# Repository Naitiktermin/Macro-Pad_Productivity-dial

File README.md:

# Macro-Pad_Productivity-dial
Schematics and code for a macro pad with a productivity dial.

Macro-Pad Top-
  Top View:

  Bottom View:

Macro-Pad Base-
    Top View:

  Bottom View:

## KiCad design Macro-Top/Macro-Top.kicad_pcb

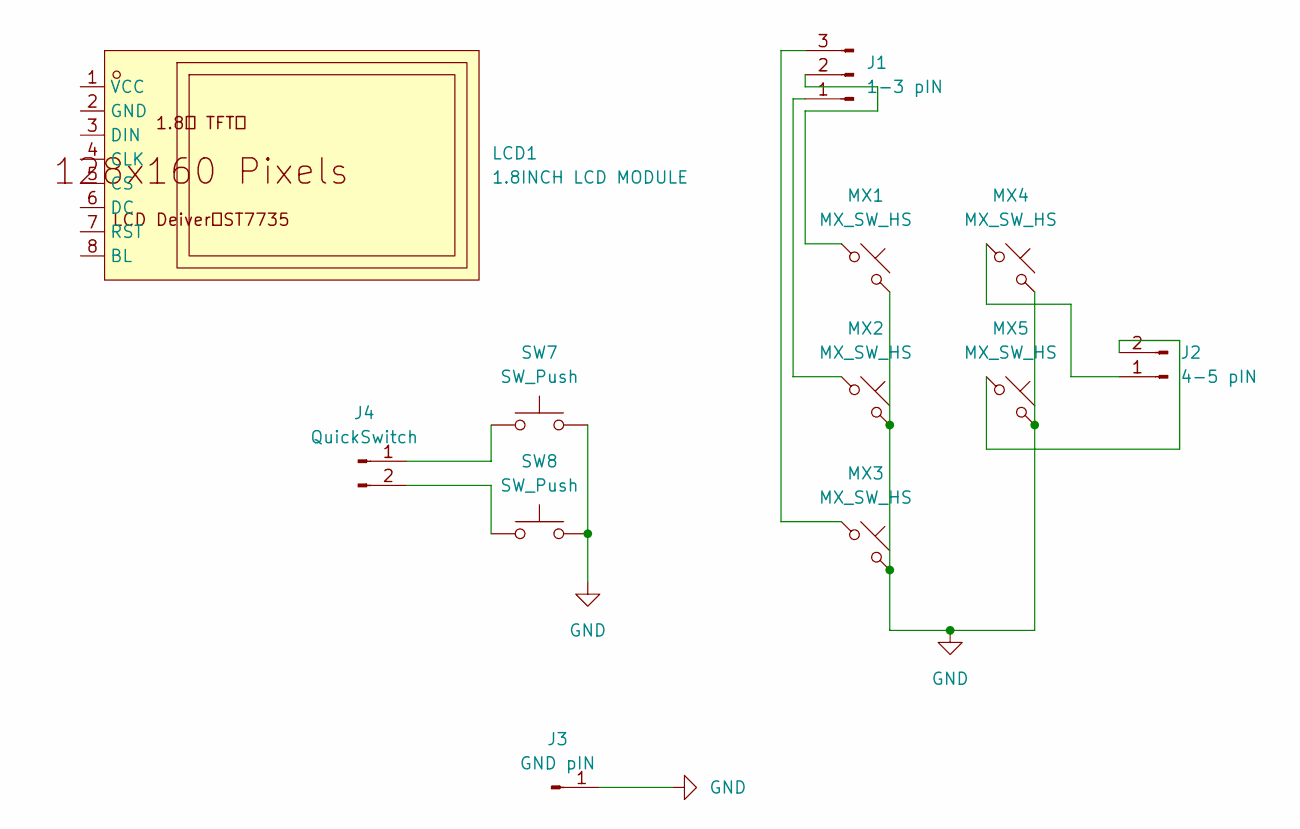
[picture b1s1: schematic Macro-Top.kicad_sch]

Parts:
J1: 1-3 pIN; PinHeader_1x03_P2.54mm_Vertical
J2: 4-5 pIN; PinHeader_1x02_P2.54mm_Vertical
J3: GND pIN; PinHeader_1x01_P2.54mm_Vertical
J4: QuickSwitch; PinHeader_1x02_P2.54mm_Horizontal
LCD1: 1.8INCH LCD MODULE; LCD-TH_L56.5-W34.0_1-8INCH-LCD-MODULE; MPN 1.8inch LCD Module; LCSC Part C359940
MX1, MX2, MX3, MX4, MX5: MX_SW_HS; SW_MX_HS_CPG151101S11_1u
SW7, SW8: SW_Push; SW_PUSH_6mm

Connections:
GND: J3.1 (Pin_1_1), MX1.2, MX2.2, MX3.2, MX4.2, MX5.2, SW7.2, SW8.2
unnamed: J1.1, MX2.1
unnamed: J1.2, MX1.1
unnamed: J1.3, MX3.1
unnamed: J2.1, MX4.1
unnamed: J2.2, MX5.1
unnamed: J4.1, SW7.1
unnamed: J4.2, SW8.1

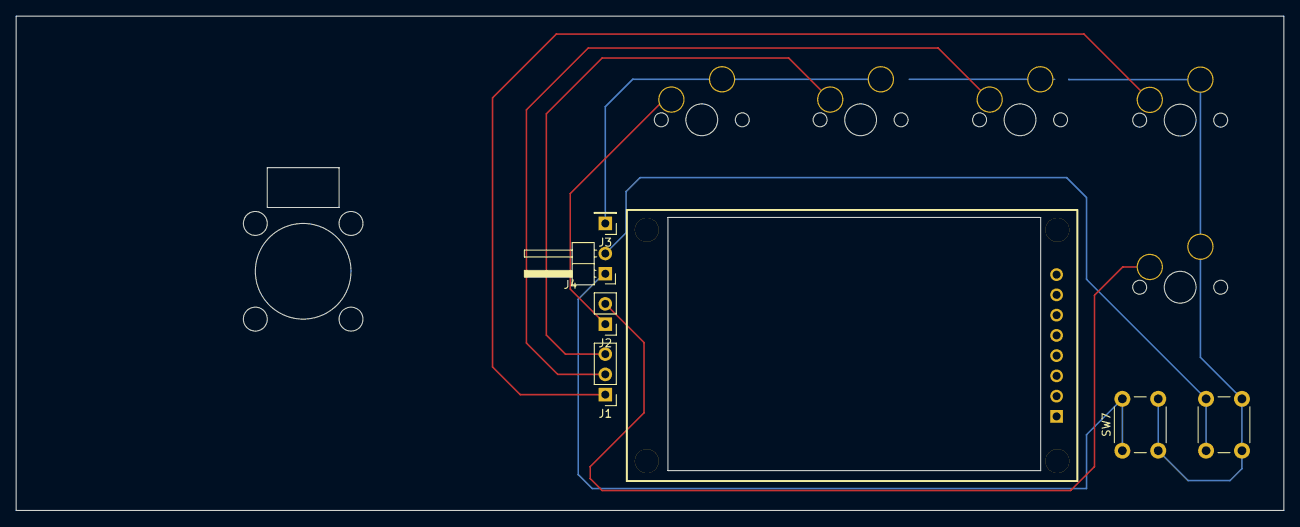
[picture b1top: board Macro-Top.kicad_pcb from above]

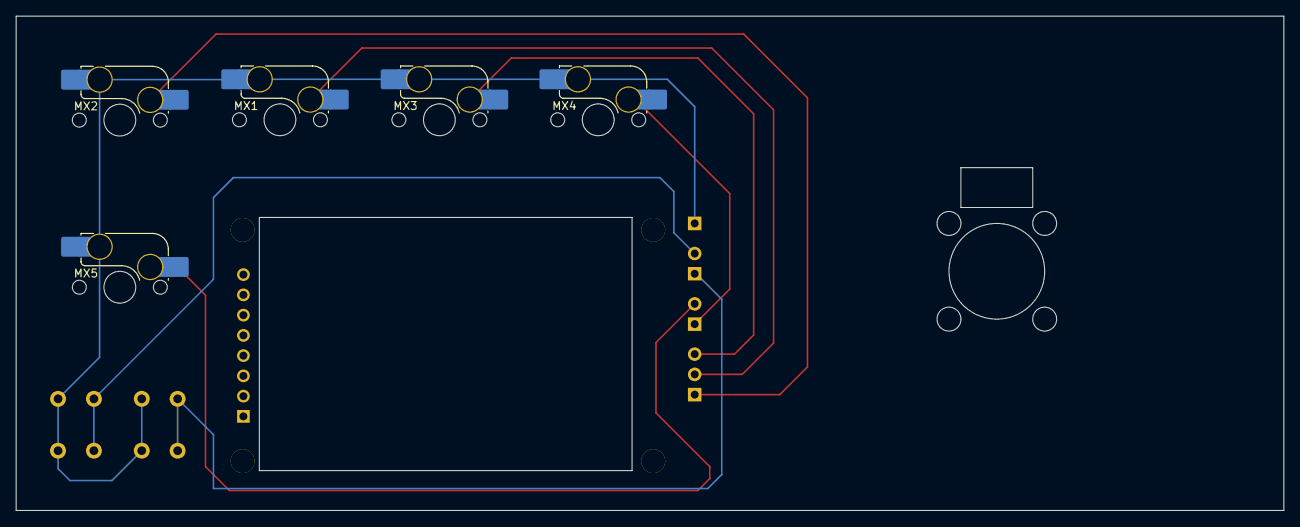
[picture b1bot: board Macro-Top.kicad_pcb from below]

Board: 2 copper layers, 159.0 x 62.0 mm, 12 parts (5 on the bottom side), 8 nets.

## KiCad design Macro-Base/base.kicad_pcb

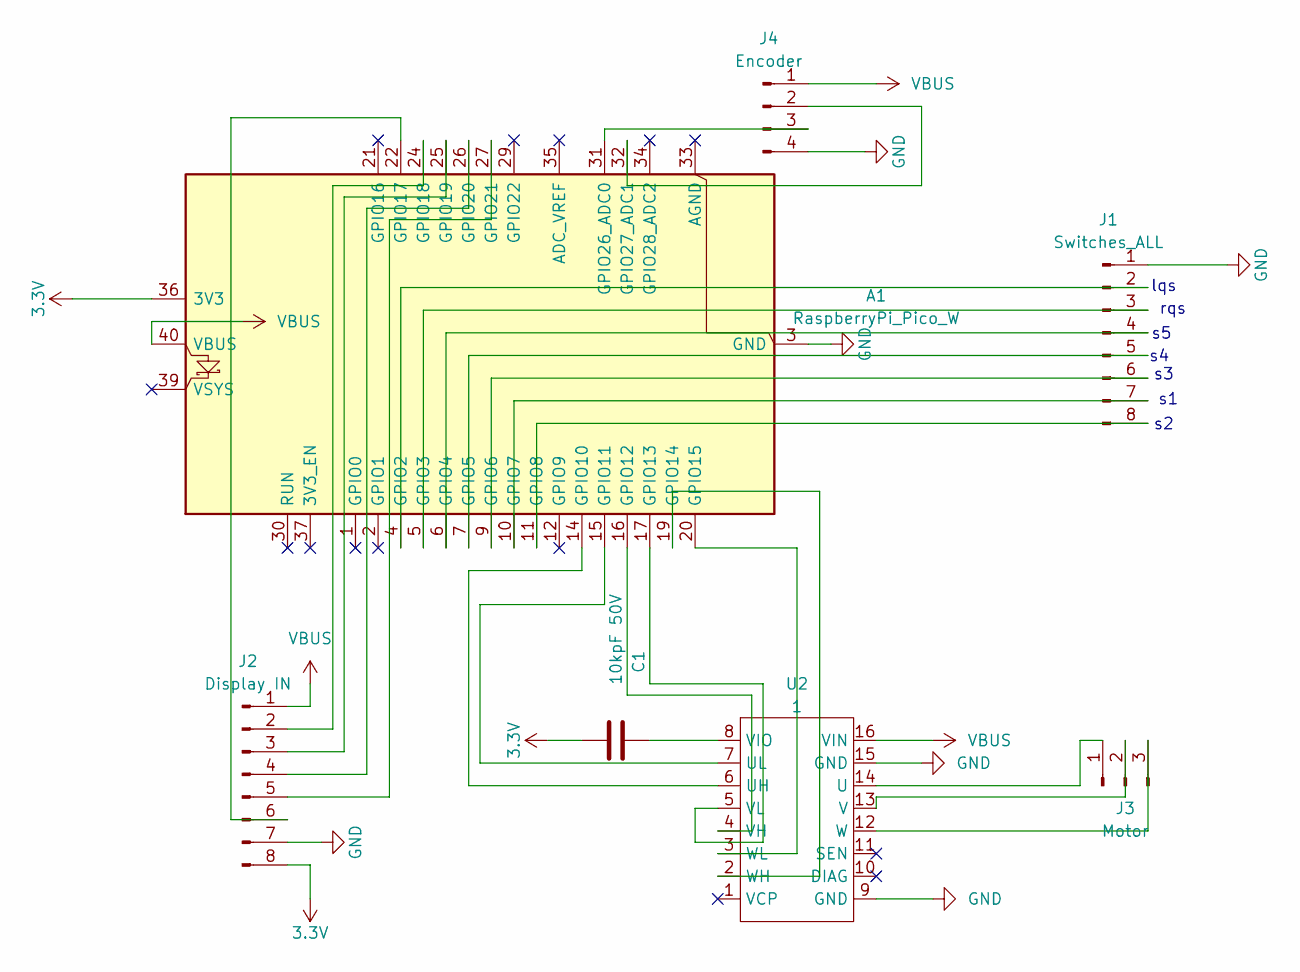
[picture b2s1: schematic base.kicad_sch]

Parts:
A1: RaspberryPi_Pico_W; RaspberryPi_Pico_W_SMD_HandSolder
C1: 10kpF 50V; C_0603_1608Metric_Pad1.08x0.95mm_HandSolder
J1: Switches_ALL; PinHeader_1x08_P2.54mm_Vertical
J2: Display IN; PinHeader_1x08_P2.54mm_Vertical
J3: Motor; PinHeader_1x03_P2.54mm_Vertical
J4: Encoder; PinHeader_1x04_P2.54mm_Vertical
U2: 1; Untitled

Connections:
3.3V: A1.36 (3V3), C1.2, J2.8
GND: A1.3 (GND), A1.8 (GND), A1.13 (GND), A1.18 (GND), A1.23 (GND), A1.28 (GND), A1.38 (GND), J1.1, J2.7, J4.4, U2.9 (GND), U2.15 (GND)
unnamed: A1.4 (GPIO2), J1.2
unnamed: A1.5 (GPIO3), J1.3
unnamed: A1.6 (GPIO4), J1.4
unnamed: A1.7 (GPIO5), J1.5
unnamed: A1.9 (GPIO6), J1.6
unnamed: A1.10 (GPIO7), J1.7
unnamed: A1.11 (GPIO8), J1.8
unnamed: A1.14 (GPIO10), U2.6 (UH)
unnamed: A1.15 (GPIO11), U2.7 (UL)
unnamed: A1.16 (GPIO12), U2.4 (VH)
unnamed: A1.17 (GPIO13), U2.5 (VL)
unnamed: A1.19 (GPIO14), U2.2 (WH)
unnamed: A1.20 (GPIO15), U2.3 (WL)
unnamed: A1.22 (GPIO17), J2.6
unnamed: A1.24 (GPIO18), J2.2
unnamed: A1.25 (GPIO19), J2.3
unnamed: A1.26 (GPIO20), J2.4
unnamed: A1.27 (GPIO21), J2.5
unnamed: A1.31 (GPIO26_ADC0), J4.3
unnamed: A1.32 (GPIO27_ADC1), J4.2
unnamed: J3.1, U2.14 (U)
unnamed: J3.2, U2.13 (V)
unnamed: J3.3, U2.12 (W)
unnamed: C1.1, U2.8 (VIO)
VBUS: A1.40 (VBUS), J2.1, J4.1, U2.16 (VIN)

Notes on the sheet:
rqs
lqs

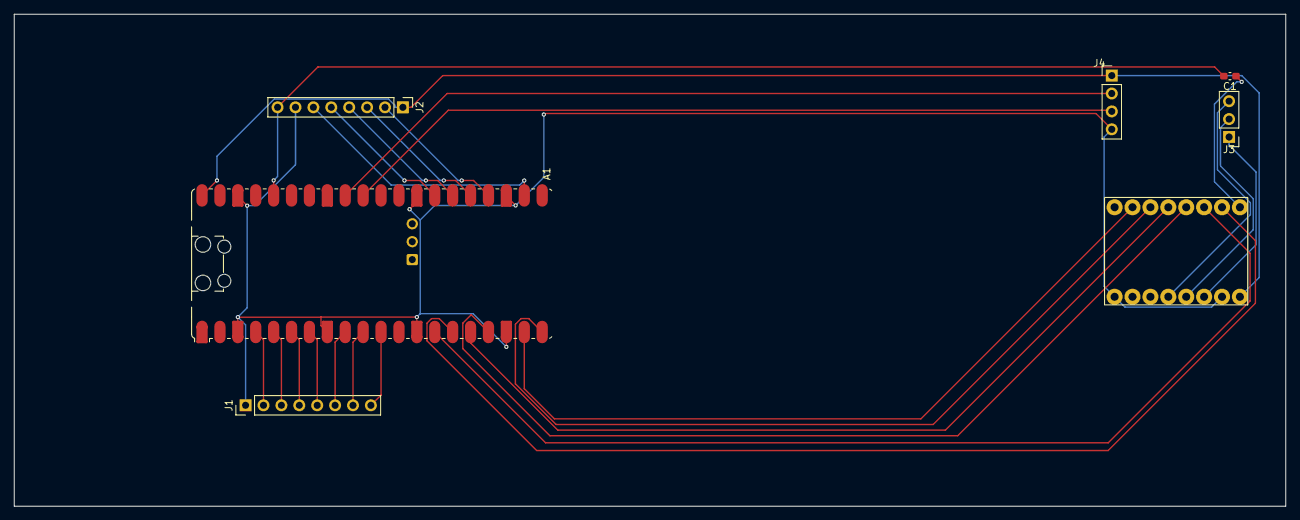
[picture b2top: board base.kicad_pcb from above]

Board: 2 copper layers, 180.4 x 69.8 mm, 7 parts (0 on the bottom side), 27 nets.
